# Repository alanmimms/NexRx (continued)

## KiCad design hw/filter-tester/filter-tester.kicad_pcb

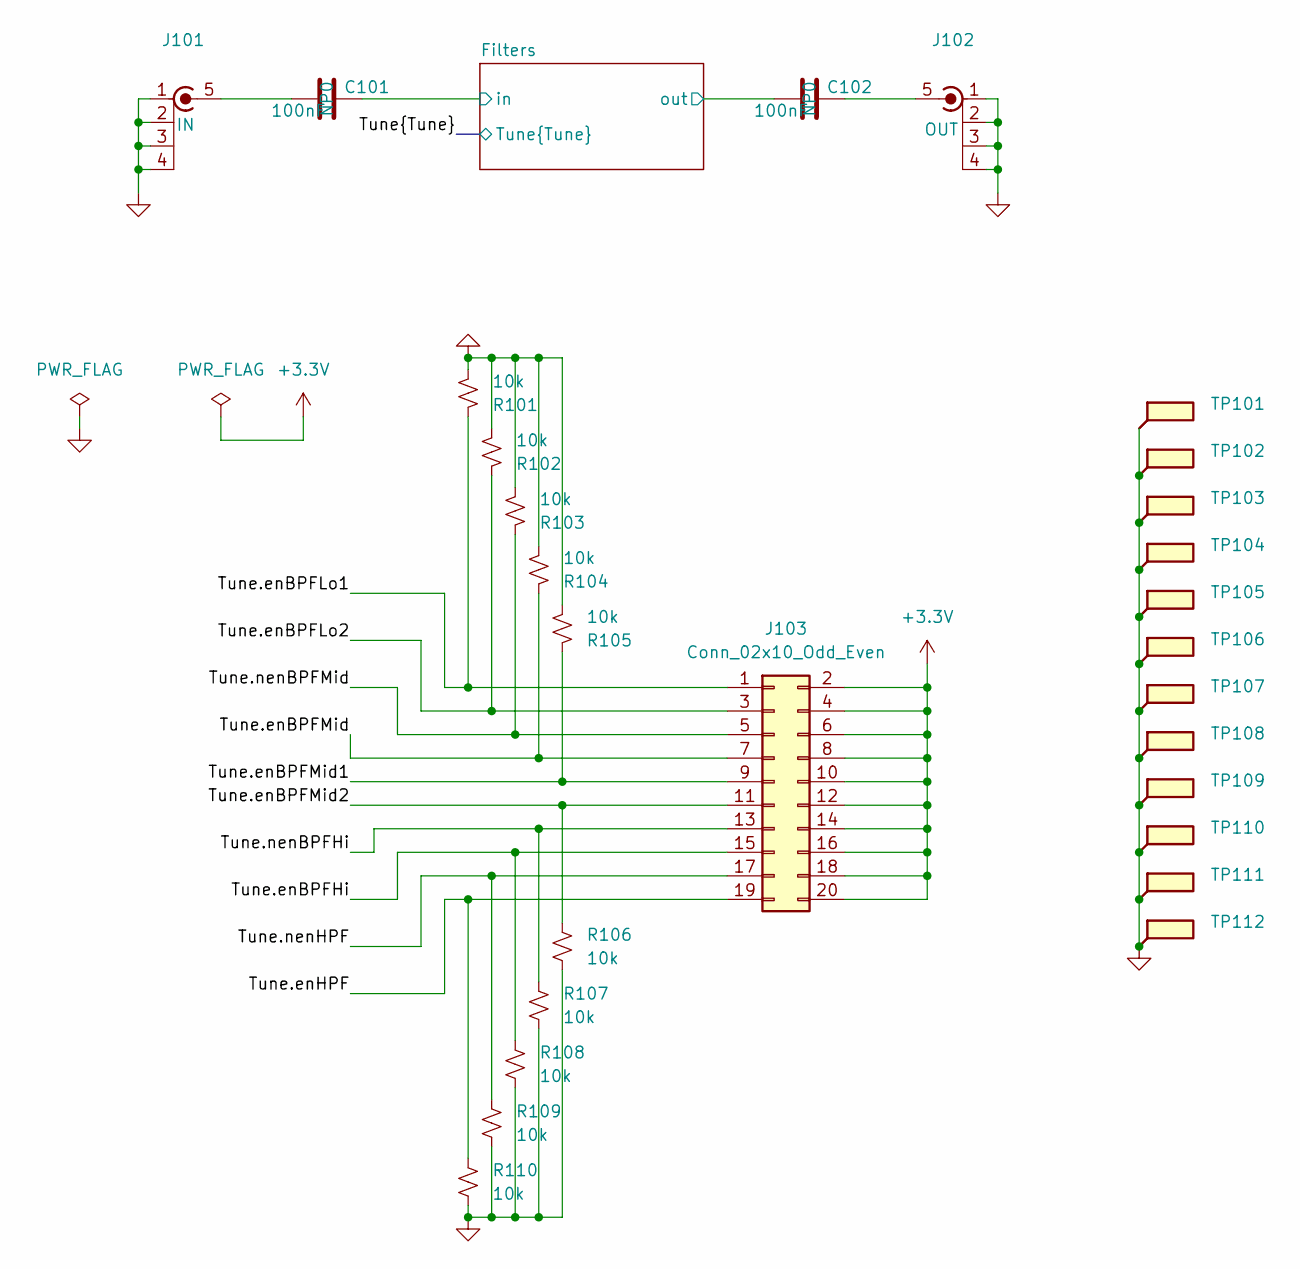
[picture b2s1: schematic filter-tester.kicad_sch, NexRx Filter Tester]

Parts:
C101, C102: 100nF; C_1206_3216Metric; MPN GRM3195C2A104JA01D; LCSC_PN C170182
J101, J102: SMA; 733910083; MPN 73391-0083; Mouser_PN 538-73391-0083
J103: Conn_02x10_Odd_Even; PinHeader_2x10_P2.54mm_Vertical_SMD; Mouser_PN 855-M20-8761046
R101, R102, R103, R104, R105, R106, R107, R108, R109, R110: 10k; R_0603_1608Metric; MPN RC0402JR-7D10KL; Mouser_PN 603-RC0402JR-7D10KL
TP101, TP102, TP103, TP104, TP105, TP106, TP107, TP108, TP109, TP110, TP111, TP112: GND; TestPoint_Pad_1.0x1.0mm

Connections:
+3.3V: J103.2, J103.4, J103.6, J103.8, J103.10, J103.12, J103.14, J103.16, J103.18, J103.20
/Filters/in: C101.1; also elsewhere on the board
/Filters/out: C102.2; also elsewhere on the board
/Tune.enBPFHi: J103.15, R108.1; also elsewhere on the board
/Tune.enBPFLo1: J103.1, R101.1; also elsewhere on the board
/Tune.enBPFLo2: J103.3, R102.1; also elsewhere on the board
/Tune.enBPFMid: J103.7, R104.1; also elsewhere on the board
/Tune.enBPFMid1: J103.9, R105.1; also elsewhere on the board
/Tune.enBPFMid2: J103.11, R106.1; also elsewhere on the board
/Tune.enHPF: J103.19, R110.1; also elsewhere on the board
/Tune.nenBPFHi: J103.13, R107.1; also elsewhere on the board
/Tune.nenBPFMid: J103.5, R103.1; also elsewhere on the board
/Tune.nenHPF: J103.17, R109.1; also elsewhere on the board
GND: J101.1 (In), J101.2 (Ext), J101.3 (Ext), J101.4 (Ext), J102.1 (In), J102.2 (Ext), J102.3 (Ext), J102.4 (Ext), R101.2, R102.2, R103.2, R104.2, R105.2, R106.2, R107.2, R108.2, R109.2, R110.2, TP101.1, TP102.1, TP103.1, TP104.1, TP105.1, TP106.1, TP107.1, TP108.1, TP109.1, TP110.1, TP111.1, TP112.1; also elsewhere on the board
unnamed: C101.2, J101.5 (Ext)
unnamed: C102.1, J102.5 (Ext)

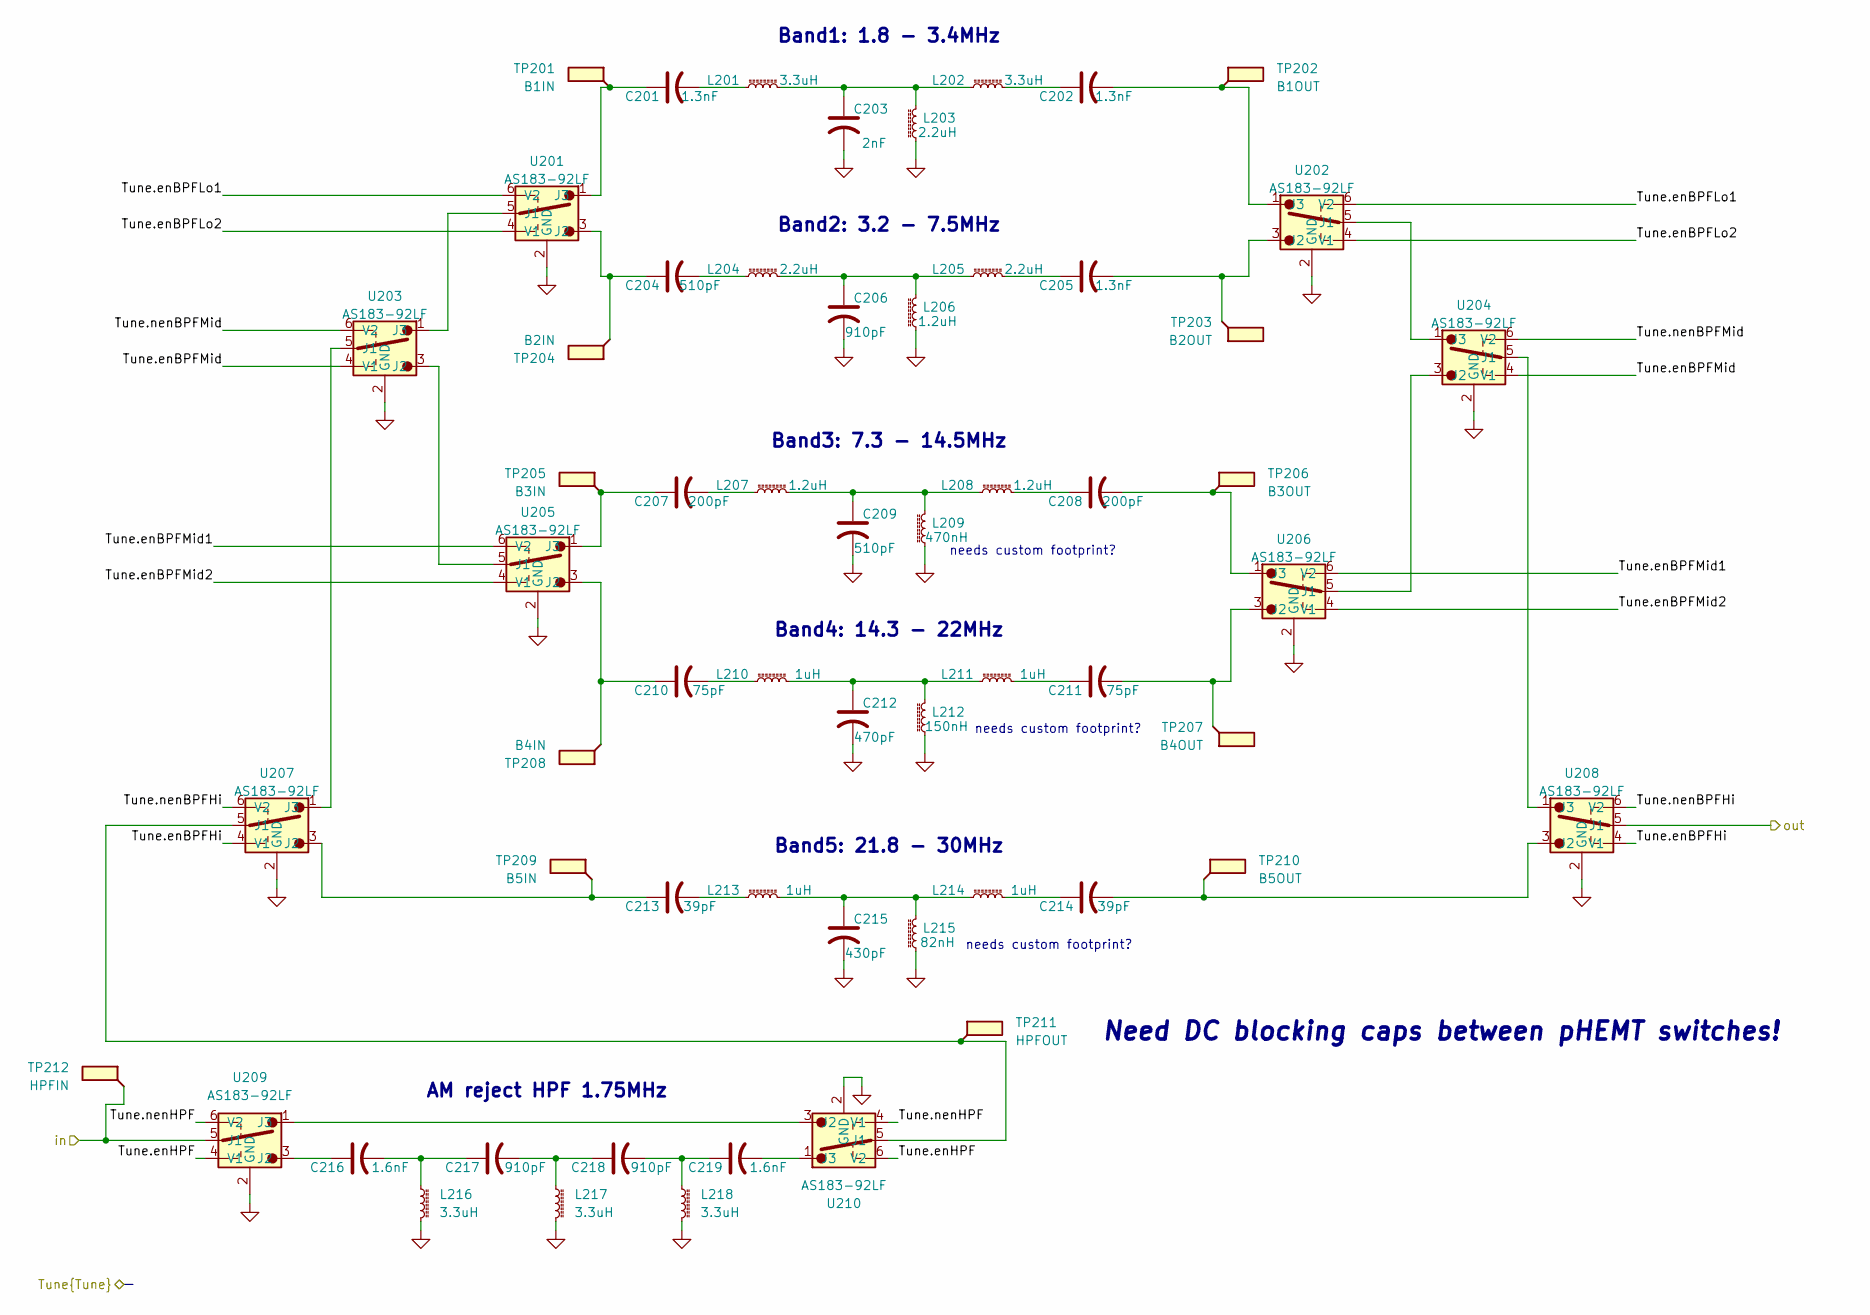
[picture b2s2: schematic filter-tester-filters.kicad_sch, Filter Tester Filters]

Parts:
C201, C202, C205: 1.3nF; C_0402_1005Metric; MPN C0402C132J5GACTU; Mouser_PN 80-C0402C132J5GACTU
C203: 2nF; C_0402_1005Metric; MPN C0402C202J3GACTU; Mouser_PN 80-C0402C202J3G
C204, C209: 510pF; C_0402_1005Metric; MPN GRT1555C1H511FA02D; Mouser_PN 81-GRT1555C1H511FA2D
C206: 910pF; C_0402_1005Metric; MPN GRT1555C1H911FA02D; Mouser_PN 81-GRT1555C1H911FA2D
C207, C208: 200pF; C_0402_1005Metric; MPN GCM1555C1H201FA16D; Mouser_PN 81-GCM1555C1H201FA6D
C210, C211: 75pF; C_0402_1005Metric; MPN GCM1555C1H750FA16J; Mouser_PN 81-GCM1555C1H750FA6J
C212: 470pF; C_0402_1005Metric; MPN GRM1555C2A471GE01D; Mouser_PN 81-GRM1555C2A471GE1D
C213, C214: 39pF; C_0402_1005Metric; MPN GRM1555C2A390JA01D; Mouser_PN 81-GRM1555C2A390JA1D
C215: 430pF; C_0402_1005Metric; MPN GRT1555C1H431FA02D; Mouser_PN 81-GRT1555C1H431FA2D
C216, C219: 1.6nF; C_0805_2012Metric; MPN GRM2165C1H162JA01D; Mouser_PN 81-GRM2165C1H162JA1D
C217, C218: 910pF; C_0805_2012Metric; MPN 08051A911JAT2A; Mouser_PN 581-08051A911JAT2A
L201, L202, L216, L217, L218: 3.3uH; L_1812_4532Metric-keepout; MPN 1812CS-332XJR; Mouser_PN 994-1812CS-332XJRC
L203, L204, L205: 2.2uH; L_1812_4532Metric-keepout; MPN 1812CS-222XJR; Mouser_PN 994-1812CS-222XJRC
L206, L207, L208: 1.2uH; L_1812_4532Metric-keepout; MPN 1812CS-122XJR; Mouser_PN 994-1812CS-122XJRC
L209: 470nH; L_1206_3216Metric-keepout; MPN AISC-1206-R47G-T; Mouser_PN 994-1206CS-471XJRC
L210, L211, L213, L214: 1uH; L_1812_4532Metric-keepout; MPN 1812CS-102XJR; Mouser_PN 994-1812CS-102XJRC
L212: 150nH; L_1206_3216Metric-keepout; MPN AISC-1206-R15G-T; Mouser_PN 994-1206CS-151XJRC
L215: 82nH; L_1206_3216Metric-keepout; MPN AISC-1206-82NK-T; Mouser_PN 994-1206CS-820XJRC
TP201: B1IN; TestPoint_Pad_1.0x1.0mm
TP202: B1OUT; TestPoint_Pad_1.0x1.0mm
TP203: B2OUT; TestPoint_Pad_1.0x1.0mm
TP204: B2IN; TestPoint_Pad_1.0x1.0mm
TP205: B3IN; TestPoint_Pad_1.0x1.0mm
TP206: B3OUT; TestPoint_Pad_1.0x1.0mm
TP207: B4OUT; TestPoint_Pad_1.0x1.0mm
TP208: B4IN; TestPoint_Pad_1.0x1.0mm
TP209: B5IN; TestPoint_Pad_1.0x1.0mm
TP210: B5OUT; TestPoint_Pad_1.0x1.0mm
TP211: HPFOUT; TestPoint_Pad_1.0x1.0mm
TP212: HPFIN; TestPoint_Pad_1.0x1.0mm
U201, U202, U203, U204, U205, U206, U207, U208, U209, U210: AS183-92LF; SOT65P220X110-6N; MPN AS183-92LF; LCSC_PN C2654768

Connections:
/Filters/in: TP212.1, U209.5 (J1); also elsewhere on the board
/Filters/out: U208.5 (J1); also elsewhere on the board
/Tune.enBPFHi: U207.4 (V1), U208.4 (V1); also elsewhere on the board
/Tune.enBPFLo1: U201.6 (V2), U202.6 (V2); also elsewhere on the board
/Tune.enBPFLo2: U201.4 (V1), U202.4 (V1); also elsewhere on the board
/Tune.enBPFMid: U203.4 (V1), U204.4 (V1); also elsewhere on the board
/Tune.enBPFMid1: U205.6 (V2), U206.6 (V2); also elsewhere on the board
/Tune.enBPFMid2: U205.4 (V1), U206.4 (V1); also elsewhere on the board
/Tune.enHPF: U209.4 (V1), U210.6 (V2); also elsewhere on the board
/Tune.nenBPFHi: U207.6 (V2), U208.6 (V2); also elsewhere on the board
/Tune.nenBPFMid: U203.6 (V2), U204.6 (V2); also elsewhere on the board
/Tune.nenHPF: U209.6 (V2), U210.4 (V1); also elsewhere on the board
GND: C203.2, C206.2, C209.2, C212.2, C215.2, L203.1, L206.1, L209.1, L212.1, L215.1, L216.2, L217.2, L218.2, U201.2 (GND), U202.2 (GND), U203.2 (GND), U204.2 (GND), U205.2 (GND), U206.2 (GND), U207.2 (GND), U208.2 (GND), U209.2 (GND), U210.2 (GND); also elsewhere on the board
unnamed: C201.2, L201.1
unnamed: C202.1, L202.2
unnamed: C203.1, L201.2, L202.1, L203.2
unnamed: C204.2, L204.1
unnamed: C205.1, L205.2
unnamed: C206.1, L204.2, L205.1, L206.2
unnamed: C207.2, L207.1
unnamed: C208.1, L208.2
unnamed: C209.1, L207.2, L208.1, L209.2
unnamed: C210.2, L210.1
unnamed: C211.1, L211.2
unnamed: C212.1, L210.2, L211.1, L212.2
unnamed: C213.2, L213.1
unnamed: C214.1, L214.2
unnamed: C215.1, L213.2, L214.1, L215.2
unnamed: C216.2, C217.1, L216.1
unnamed: C217.2, C218.1, L217.1
unnamed: C218.2, C219.1, L218.1
unnamed: U201.5 (J1), U203.1 (J3)
unnamed: C204.1, TP204.1, U201.3 (J2)
unnamed: C201.1, TP201.1, U201.1 (J3)
unnamed: U202.5 (J1), U204.1 (J3)
unnamed: C205.2, TP203.1, U202.3 (J2)
unnamed: C202.2, TP202.1, U202.1 (J3)
unnamed: U203.5 (J1), U207.1 (J3)
unnamed: U203.3 (J2), U205.5 (J1)
unnamed: U204.5 (J1), U208.1 (J3)
unnamed: U204.3 (J2), U206.5 (J1)
unnamed: C210.1, TP208.1, U205.3 (J2)
unnamed: C207.1, TP205.1, U205.1 (J3)
unnamed: C211.2, TP207.1, U206.3 (J2)
unnamed: C208.2, TP206.1, U206.1 (J3)
unnamed: TP211.1, U207.5 (J1), U210.5 (J1)
unnamed: C213.1, TP209.1, U207.3 (J2)
unnamed: C214.2, TP210.1, U208.3 (J2)
unnamed: C216.1, U209.3 (J2)
unnamed: U209.1 (J3), U210.3 (J2)
unnamed: C219.2, U210.1 (J3)

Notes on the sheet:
needs custom footprint?
AM reject HPF 1.75MHz
Band4: 14.3 - 22MHz
Need DC blocking caps between pHEMT switches!
Band3: 7.3 - 14.5MHz
Band2: 3.2 - 7.5MHz
Band5: 21.8 - 30MHz
Band1: 1.8 - 3.4MHz

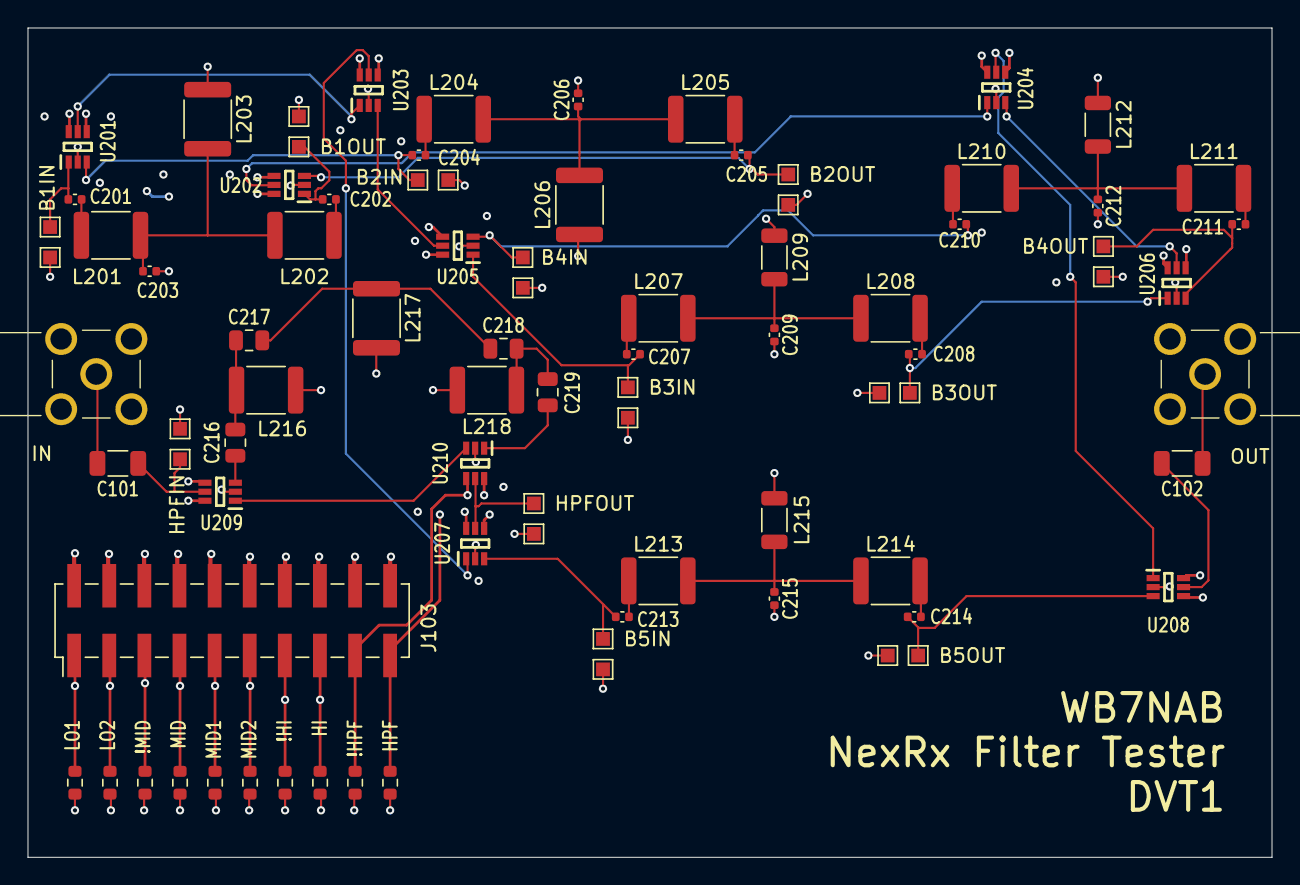
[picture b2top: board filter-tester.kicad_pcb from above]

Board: 6 copper layers, 90.0 x 60.0 mm, 86 parts (0 on the bottom side), 54 nets.

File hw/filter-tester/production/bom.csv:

Designator,Footprint,Quantity,Value,LCSC Part #
"C101, C102",1206,2,100nF,GRM3195C2A104JA01D
"C201, C202, C205",0402,3,1.3nF,C0402C132J5GACTU
C203,0402,1,2nF,C0402C202J3GACTU
"C204, C209",0402,2,510pF,GRT1555C1H511FA02D
C206,0402,1,910pF,GRT1555C1H911FA02D
"C207, C208",0402,2,200pF,GCM1555C1H201FA16D
"C210, C211",0402,2,75pF,GCM1555C1H750FA16J
C212,0402,1,470pF,GRM1555C2A471GE01D
"C213, C214",0402,2,39pF,GRM1555C2A390JA01D
C215,0402,1,430pF,GRT1555C1H431FA02D
"C216, C219",0805,2,1.6nF,GRM2165C1H162JA01D
"C217, C218",0805,2,910pF,08051A911JAT2A
"J101, J102",733910083,2,SMA,73391-0083
J103,PinHeader_2x10_P2.54mm_Vertical_SMD,1,Conn_02x10_Odd_Even,M20-8761046
"L201, L202, L216, L217, L218",1812,5,3.3uH,1812CS-332XJR
"L203, L204",1812,2,2.2uH,1812CS-222XJR
L205,1812,1,"2,2uH",1812CS-222XJR
"L206, L207, L208",1812,3,1.2uH,1812CS-122XJR
L209,1206,1,470nH,1206CS-471XJR
"L210, L211, L213, L214",1812,4,1uH,1812CS-102XJR
L212,1206,1,150nH,1206CS-151XJR
L215,1206,1,82nH,1206CS-820XJR
"R101, R102, R103, R104, R105, R106, R107, R108, R109, R110",0603,10,10k,RC0402JR-7D10KL
"TP101, TP102, TP103, TP104, TP105, TP106, TP107, TP108, TP109, TP110, TP111, TP112",TestPoint_Pad_1.0x1.0mm,12,GND,
TP201,TestPoint_Pad_1.0x1.0mm,1,B1IN,
TP202,TestPoint_Pad_1.0x1.0mm,1,B1OUT,
TP203,TestPoint_Pad_1.0x1.0mm,1,B2OUT,
TP204,TestPoint_Pad_1.0x1.0mm,1,B2IN,
TP205,TestPoint_Pad_1.0x1.0mm,1,B3IN,
TP206,TestPoint_Pad_1.0x1.0mm,1,B3OUT,
TP207,TestPoint_Pad_1.0x1.0mm,1,B4OUT,
TP208,TestPoint_Pad_1.0x1.0mm,1,B4IN,
TP209,TestPoint_Pad_1.0x1.0mm,1,B5IN,
TP210,TestPoint_Pad_1.0x1.0mm,1,B5OUT,
TP211,TestPoint_Pad_1.0x1.0mm,1,HPFOUT,
TP212,TestPoint_Pad_1.0x1.0mm,1,HPFIN,
"U201, U202, U203, U204, U205, U206, U207, U208, U209, U210",SOT65P220X110-6N,10,AS183-92LF,AS183-92LF

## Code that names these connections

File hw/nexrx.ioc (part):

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Mcu.Name=STM32H753VITx
Mcu.Package=LQFP100
Mcu.UserName=STM32H753VITx
PA0.GPIOParameters=GPIO_Label
PA0.GPIO_Label=osd0.data
PA0.Mode=SAI_B_MasterWithClock
PA0.Signal=SAI2_SD_B
PA1.GPIOParameters=GPIO_Label
PA1.GPIO_Label=osdMCLK
PA1.Mode=SAI_B_MasterWithClock
PA1.Signal=SAI2_MCLK_B
PA11.GPIOParameters=GPIO_Label
PA11.GPIO_Label=dispNSS
PA11.Mode=NSS_Signal_Hard_Output
PA11.Signal=SPI2_NSS
PA12.GPIOParameters=GPIO_Label
PA12.GPIO_Label=osdWCLK
PA12.Mode=SAI_B_MasterWithClock
PA12.Signal=SAI2_FS_B
PA13\ (JTMS/SWDIO).GPIOParameters=GPIO_Label
PA13\ (JTMS/SWDIO).GPIO_Label=SWDIO
PA13\ (JTMS/SWDIO).Mode=Serial_Wire
PA13\ (JTMS/SWDIO).Signal=DEBUG_JTMS-SWDIO
PA14\ (JTCK/SWCLK).GPIOParameters=GPIO_Label
PA14\ (JTCK/SWCLK).GPIO_Label=SWCL
PA14\ (JTCK/SWCLK).Mode=Serial_Wire
PA14\ (JTCK/SWCLK).Signal=DEBUG_JTCK-SWCLK
PA15\ (JTDI).GPIOParameters=GPIO_Speed,PinState,GPIO_Label
PA15\ (JTDI).GPIO_Label=cpld1.NSS
PA15\ (JTDI).GPIO_Speed=GPIO_SPEED_FREQ_MEDIUM
PA15\ (JTDI).PinState=GPIO_PIN_SET
PA15\ (JTDI).Signal=GPIO_Output
PA2.GPIOParameters=GPIO_Speed,GPIO_Label
PA2.GPIO_Label=osdBCLK
PA2.GPIO_Speed=GPIO_SPEED_FREQ_HIGH
PA2.Mode=SAI_B_MasterWithClock
PA2.Signal=SAI2_SCK_B
PA3.GPIOParameters=GPIO_Label
PA3.GPIO_Label=usbDATA0
PA3.Mode=Device_HS
PA3.Signal=USB_OTG_HS_ULPI_D0
PA4.GPIOParameters=GPIO_Speed,PinState,GPIO_Label
PA4.GPIO_Label=cpld0.NSS
PA4.GPIO_Speed=GPIO_SPEED_FREQ_MEDIUM
PA4.PinState=GPIO_PIN_SET
PA4.Signal=GPIO_Output
PA5.GPIOParameters=GPIO_Label
PA5.GPIO_Label=usbCLKOUT
PA5.Mode=Device_HS
PA5.Signal=USB_OTG_HS_ULPI_CK
PA6.GPIOParameters=GPIO_Label
PA6.GPIO_Label=adcReset
PA6.Signal=GPIO_Output
PA7.GPIOParameters=GPIO_Label
PA7.GPIO_Label=cc2ADC
PA7.Signal=ADCx_INP7
PA9.GPIOParameters=GPIO_Label
PA9.GPIO_Label=dispSCK
PA9.Mode=TX_Only_Simplex_Unidirect_Master
PA9.Signal=SPI2_SCK
PB0.GPIOParameters=GPIO_Label
PB0.GPIO_Label=usbDATA1
PB0.Mode=Device_HS
PB0.Signal=USB_OTG_HS_ULPI_D1
PB1.GPIOParameters=GPIO_Label
PB1.GPIO_Label=usbDATA2
PB1.Mode=Device_HS
PB1.Signal=USB_OTG_HS_ULPI_D2
PB10.GPIOParameters=GPIO_Label
PB10.GPIO_Label=usbDATA3
PB10.Mode=Device_HS
PB10.Signal=USB_OTG_HS_ULPI_D3
PB11.GPIOParameters=GPIO_Label
PB11.GPIO_Label=usbDATA4
PB11.Mode=Device_HS
PB11.Signal=USB_OTG_HS_ULPI_D4
PB12.GPIOParameters=GPIO_Label
PB12.GPIO_Label=usbDATA5
PB12.Mode=Device_HS
PB12.Signal=USB_OTG_HS_ULPI_D5
PB13.GPIOParameters=GPIO_Label
PB13.GPIO_Label=usbDATA6
PB13.Mode=Device_HS
PB13.Signal=USB_OTG_HS_ULPI_D6
PB14.GPIOParameters=GPIO_Label
PB14.GPIO_Label=factoryTX
PB14.Mode=Asynchronous
PB14.Signal=USART1_TX
PB15.GPIOParameters=GPIO_Label
PB15.GPIO_Label=factoryRX
PB15.Mode=Asynchronous
PB15.Signal=USART1_RX
PB2.GPIOParameters=GPIO_Speed,GPIO_Label
PB2.GPIO_Label=cpld.MOSI
PB2.GPIO_Speed=GPIO_SPEED_FREQ_HIGH
PB2.Mode=Full_Duplex_Master
PB2.Signal=SPI3_MOSI
PB3\ (JTDO/TRACESWO).GPIOParameters=GPIO_Label
PB3\ (JTDO/TRACESWO).GPIO_Label=gnssRESET
PB3\ (JTDO/TRACESWO).Signal=GPIO_Output
PB4\ (NJTRST).GPIOParameters=GPIO_Label
PB4\ (NJTRST).GPIO_Label=clkOEB
PB4\ (NJTRST).Signal=GPIO_Output
PB5.GPIOParameters=GPIO_Label
PB5.GPIO_Label=usbDATA7
PB5.Mode=Device_HS
PB5.Signal=USB_OTG_HS_ULPI_D7
PB6.GPIOParameters=GPIO_Label
PB6.GPIO_Label=clk.SCL
PB6.Mode=I2C
PB6.Signal=I2C1_SCL
PB7.GPIOParameters=GPIO_Label
PB7.GPIO_Label=clk.SDA
PB7.Mode=I2C
PB7.Signal=I2C1_SDA
PB8.GPIOParameters=GPIO_Label
PB8.GPIO_Label=mcuGRN
PB8.Signal=S_TIM16_CH1
PB9.GPIOParameters=GPIO_Label
PB9.GPIO_Label=mcuRED
PB9.Signal=S_TIM17_CH1
PC0.GPIOParameters=GPIO_Label
PC0.GPIO_Label=usbSTP
PC0.Mode=Device_HS
PC0.Signal=USB_OTG_HS_ULPI_STP
PC1.GPIOParameters=GPIO_Label
PC1.GPIO_Label=dispMOSI
PC1.Mode=TX_Only_Simplex_Unidirect_Master
PC1.Signal=SPI2_MOSI
PC10.GPIOParameters=GPIO_Speed,GPIO_Label
PC10.GPIO_Label=cpld.SCK
PC10.GPIO_Speed=GPIO_SPEED_FREQ_HIGH
PC10.Mode=Full_Duplex_Master
PC10.Signal=SPI3_SCK
PC11.GPIOParameters=GPIO_Speed,GPIO_Label
PC11.GPIO_Label=cpld.MISO
PC11.GPIO_Speed=GPIO_SPEED_FREQ_HIGH
PC11.Mode=Full_Duplex_Master
PC11.Signal=SPI3_MISO
PC2_C.GPIOParameters=GPIO_Label
PC2_C.GPIO_Label=usbDIR
PC2_C.Mode=Device_HS
PC2_C.Signal=USB_OTG_HS_ULPI_DIR
PC3_C.GPIOParameters=GPIO_Label
PC3_C.GPIO_Label=usbNXT
PC3_C.Mode=Device_HS
PC3_C.Signal=USB_OTG_HS_ULPI_NXT
PC5.GPIOParameters=GPIO_Label
PC5.GPIO_Label=cc1ADC
PC5.Signal=ADCx_INP8
PC7.GPIOParameters=GPIO_Label
PC7.GPIO_Label=dispBL
PC7.Signal=S_TIM3_CH2
PD0.GPIOParameters=GPIO_Label
PD0.GPIO_Label=filter.BPF2
PD0.Signal=GPIO_Output
PD1.GPIOParameters=GPIO_Label
PD1.GPIO_Label=filter.BPF1
PD1.Signal=GPIO_Output
PD10.GPIOParameters=GPIO_Label
PD10.GPIO_Label=atten.3dB
PD10.Signal=GPIO_Output
PD11.GPIOParameters=GPIO_Label
PD11.GPIO_Label=osd1.data
PD11.Mode=SAI_A_SyncSlave
PD11.Signal=SAI2_SD_A
PD2.GPIOParameters=GPIO_Label
PD2.GPIO_Label=filter.HPF
PD2.Signal=GPIO_Output
PD3.GPIOParameters=GPIO_Label
PD3.GPIO_Label=filter.nHPF
PD3.Signal=GPIO_Output
PD4.GPIOParameters=GPIO_Label
PD4.GPIO_Label=filter.BPF4
PD4.Signal=GPIO_Output
PD5.GPIOParameters=GPIO_Label
PD5.GPIO_Label=filter.BPF3
PD5.Signal=GPIO_Output
PD6.GPIOParameters=GPIO_Label
PD6.GPIO_Label=enable3V3
PD6.Signal=GPIO_Output
PD7.GPIOParameters=GPIO_Label
PD7.GPIO_Label=atten.6dB
PD7.Signal=GPIO_Output
PD8.GPIOParameters=GPIO_Label
PD8.GPIO_Label=atten.12dB
PD8.Signal=GPIO_Output
PD9.GPIOParameters=GPIO_Label
PD9.GPIO_Label=atten.24dB
PD9.Signal=GPIO_Output
PE0.GPIOParameters=GPIO_Label
PE0.GPIO_Label=cpldDONE
PE0.Signal=GPIO_Input
PE1.GPIOParameters=GPIO_Label
PE1.GPIO_Label=cpld.CRESET
PE1.Signal=GPIO_Output
PE12.GPIOParameters=GPIO_Label
PE12.GPIO_Label=dispRESET
PE12.Signal=GPIO_Output
PE13.GPIOParameters=GPIO_Speed,GPIO_Label
PE13.GPIO_Label=dispDC
PE13.GPIO_Speed=GPIO_SPEED_FREQ_MEDIUM
PE13.Signal=GPIO_Output
PE14.GPIOParameters=GPIO_Speed,GPIO_Label
PE14.GPIO_Label=osdMOSI
PE14.GPIO_Speed=GPIO_SPEED_FREQ_HIGH
PE14.Mode=Full_Duplex_Master
PE14.Signal=SPI4_MOSI
PE2.GPIOParameters=GPIO_Speed,GPIO_Label
PE2.GPIO_Label=osdSCK
PE2.GPIO_Speed=GPIO_SPEED_FREQ_HIGH
PE2.Mode=Full_Duplex_Master
PE2.Signal=SPI4_SCK
PE3.GPIOParameters=GPIO_Speed,GPIO_Label
PE3.GPIO_Label=osd0.NSS
PE3.GPIO_Speed=GPIO_SPEED_FREQ_MEDIUM
PE3.Signal=GPIO_Output
PE4.GPIOParameters=GPIO_Speed,GPIO_Label
PE4.GPIO_Label=osd1.NSS
PE4.GPIO_Speed=GPIO_SPEED_FREQ_MEDIUM
PE4.Signal=GPIO_Output
PE5.GPIOParameters=GPIO_Label
PE5.GPIO_Label=osdMISO
PE5.Mode=Full_Duplex_Master
PE5.Signal=SPI4_MISO
PE6.GPIOParameters=GPIO_Label
PE6.GPIO_Label=mcuBLU
PE6.Signal=S_TIM15_CH2
PE7.GPIOParameters=GPIO_Label
PE7.GPIO_Label=gnssRx
PE7.Mode=Asynchronous
PE7.Signal=UART7_RX
PE8.GPIOParameters=GPIO_Label
PE8.GPIO_Label=gnssTx
PE8.Mode=Asynchronous
PE8.Signal=UART7_TX
PH0-OSC_IN\ (PH0).Mode=HSE-External-Oscillator
PH0-OSC_IN\ (PH0).Signal=RCC_OSC_IN
PH1-OSC_OUT\ (PH1).Mode=HSE-External-Oscillator
PH1-OSC_OUT\ (PH1).Signal=RCC_OSC_OUT
RCC.SYSCLKFreq_VALUE=64000000
board=custom

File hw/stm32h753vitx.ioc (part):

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Mcu.Name=STM32H753VITx
Mcu.Package=LQFP100
Mcu.UserName=STM32H753VITx
PA0.GPIOParameters=GPIO_Label
PA0.GPIO_Label=Ctrl.qsdData2
PA0.Mode=SAI_B_SyncSlave
PA0.Signal=SAI2_SD_B
PA11.GPIOParameters=GPIO_Label
PA11.GPIO_Label=dispNSS
PA11.Mode=NSS_Signal_Hard_Output
PA11.Signal=SPI2_NSS
PA13\ (JTMS/SWDIO).GPIOParameters=GPIO_Label
PA13\ (JTMS/SWDIO).GPIO_Label=SWDIO
PA13\ (JTMS/SWDIO).Mode=Serial_Wire
PA13\ (JTMS/SWDIO).Signal=DEBUG_JTMS-SWDIO
PA14\ (JTCK/SWCLK).GPIOParameters=GPIO_Label
PA14\ (JTCK/SWCLK).GPIO_Label=SWCL
PA14\ (JTCK/SWCLK).Mode=Serial_Wire
PA14\ (JTCK/SWCLK).Signal=DEBUG_JTCK-SWCLK
PA3.GPIOParameters=GPIO_Label
PA3.GPIO_Label=usbDATA0
PA3.Mode=Device_HS
PA3.Signal=USB_OTG_HS_ULPI_D0
PA4.GPIOParameters=GPIO_Label,GPIO_Speed,GPIO_PuPd
PA4.GPIO_Label=FPGA.NSS
PA4.GPIO_PuPd=GPIO_PULLUP
PA4.GPIO_Speed=GPIO_SPEED_FREQ_HIGH
PA4.Mode=NSS_Signal_Hard_Output
PA4.Signal=SPI3_NSS
PA5.GPIOParameters=GPIO_Label
PA5.GPIO_Label=usbCLKOUT
PA5.Mode=Device_HS
PA5.Signal=USB_OTG_HS_ULPI_CK
PA6.GPIOParameters=GPIO_Label
PA6.GPIO_Label=Ctrl.audioReset
PA6.Signal=GPIO_Output
PA7.GPIOParameters=GPIO_Label
PA7.GPIO_Label=Ctrl.usbCC2adc
PA7.Signal=ADCx_INP7
PA9.GPIOParameters=GPIO_Label
PA9.GPIO_Label=dispSCK
PA9.Mode=TX_Only_Simplex_Unidirect_Master
PA9.Signal=SPI2_SCK
PB0.GPIOParameters=GPIO_Label
PB0.GPIO_Label=usbDATA1
PB0.Mode=Device_HS
PB0.Signal=USB_OTG_HS_ULPI_D1
PB1.GPIOParameters=GPIO_Label
PB1.GPIO_Label=usbDATA2
PB1.Mode=Device_HS
PB1.Signal=USB_OTG_HS_ULPI_D2
PB10.GPIOParameters=GPIO_Label
PB10.GPIO_Label=usbDATA3
PB10.Mode=Device_HS
PB10.Signal=USB_OTG_HS_ULPI_D3
PB11.GPIOParameters=GPIO_Label
PB11.GPIO_Label=usbDATA4
PB11.Mode=Device_HS
PB11.Signal=USB_OTG_HS_ULPI_D4
PB12.GPIOParameters=GPIO_Label
PB12.GPIO_Label=usbDATA5
PB12.Mode=Device_HS
PB12.Signal=USB_OTG_HS_ULPI_D5
PB13.GPIOParameters=GPIO_Label
PB13.GPIO_Label=usbDATA6
PB13.Mode=Device_HS
PB13.Signal=USB_OTG_HS_ULPI_D6
PB2.GPIOParameters=GPIO_Speed,GPIO_Label
PB2.GPIO_Label=FPGA.MOSI
PB2.GPIO_Speed=GPIO_SPEED_FREQ_HIGH
PB2.Mode=Full_Duplex_Master
PB2.Signal=SPI3_MOSI
PB5.GPIOParameters=GPIO_Label
PB5.GPIO_Label=usbDATA7
PB5.Mode=Device_HS
PB5.Signal=USB_OTG_HS_ULPI_D7
PC0.GPIOParameters=GPIO_Label
PC0.GPIO_Label=usbSTP
PC0.Mode=Device_HS
PC0.Signal=USB_OTG_HS_ULPI_STP
PC1.GPIOParameters=GPIO_Label
PC1.GPIO_Label=dispMOSI
PC1.Mode=TX_Only_Simplex_Unidirect_Master
PC1.Signal=SPI2_MOSI
PC10.GPIOParameters=GPIO_Speed,GPIO_Label
PC10.GPIO_Label=FPGA.SCK
PC10.GPIO_Speed=GPIO_SPEED_FREQ_HIGH
PC10.Mode=Full_Duplex_Master
PC10.Signal=SPI3_SCK
PC11.GPIOParameters=GPIO_Speed,GPIO_Label
PC11.GPIO_Label=FPGA.MISO
PC11.GPIO_Speed=GPIO_SPEED_FREQ_HIGH
PC11.Mode=Full_Duplex_Master
PC11.Signal=SPI3_MISO
PC2_C.GPIOParameters=GPIO_Label
PC2_C.GPIO_Label=usbDIR
PC2_C.Mode=Device_HS
PC2_C.Signal=USB_OTG_HS_ULPI_DIR
PC3_C.GPIOParameters=GPIO_Label
PC3_C.GPIO_Label=usbNXT
PC3_C.Mode=Device_HS
PC3_C.Signal=USB_OTG_HS_ULPI_NXT
PC5.GPIOParameters=GPIO_Label
PC5.GPIO_Label=Ctrl.usbCC1adc
PC5.Signal=ADCx_INP8
PC6.GPIOParameters=GPIO_Label
PC6.GPIO_Label=Tune.txrx
PC6.Mode=Half_duplex(single_wire_mode)
PC6.Signal=USART6_TX
PD0.GPIOParameters=GPIO_Speed,GPIO_Label
PD0.GPIO_Label=Ctrl.qsdBCLK
PD0.GPIO_Speed=GPIO_SPEED_FREQ_HIGH
PD0.Mode=SAI_A_MasterWithClock
PD0.Signal=SAI3_SCK_A
PD1.GPIOParameters=GPIO_Speed,GPIO_Label
PD1.GPIO_Label=Ctrl.qsdData1
PD1.GPIO_Speed=GPIO_SPEED_FREQ_HIGH
PD1.Mode=SAI_A_MasterWithClock
PD1.Signal=SAI3_SD_A
PD11.GPIOParameters=GPIO_Label
PD11.GPIO_Label=Ctrl.qsdData3
PD11.Mode=SAI_A_SyncSlave
PD11.Signal=SAI2_SD_A
PD12.GPIOParameters=GPIO_Speed,GPIO_Label
PD12.GPIO_Label=Ctrl.audioSCL
PD12.GPIO_Speed=GPIO_SPEED_FREQ_MEDIUM
PD12.Mode=I2C
PD12.Signal=I2C4_SCL
PD13.GPIOParameters=GPIO_Speed,GPIO_Label
PD13.GPIO_Label=Ctrl.audioSDA
PD13.GPIO_Speed=GPIO_SPEED_FREQ_MEDIUM
PD13.Mode=I2C
PD13.Signal=I2C4_SDA
PD15.GPIOParameters=GPIO_Speed,GPIO_Label
PD15.GPIO_Label=Ctrl.qsdMCLK
PD15.GPIO_Speed=GPIO_SPEED_FREQ_HIGH
PD15.Mode=SAI_A_MasterWithClock
PD15.Signal=SAI3_MCLK_A
PD4.GPIOParameters=GPIO_Speed,GPIO_Label
PD4.GPIO_Label=Ctrl.qsdWCLK
PD4.GPIO_Speed=GPIO_SPEED_FREQ_HIGH
PD4.Mode=SAI_A_MasterWithClock
PD4.Signal=SAI3_FS_A
PD5.Signal=GPIO_Output
PD6.GPIOParameters=GPIO_Label
PD6.GPIO_Label=Ctrl.enable3V3
PD6.Signal=GPIO_Output
PD7.GPIOParameters=GPIO_Label
PD7.GPIO_Label=Ctrl.enable3VA
PD7.Signal=GPIO_Output
PD8.GPIOParameters=GPIO_Label
PD8.GPIO_Label=Ctrl.enable5VA
PD8.Signal=GPIO_Output
PD9.GPIOParameters=GPIO_Label
PD9.GPIO_Label=Ctrl.enableFPGAVCORE
PD9.Signal=GPIO_Output
PE0.GPIOParameters=GPIO_Label
PE0.GPIO_Label=FPGA.DONE
PE0.Signal=GPIO_Input
PE1.GPIOParameters=GPIO_Label
PE1.GPIO_Label=FPGA.PROG
PE1.Signal=GPIO_Output
PE12.GPIOParameters=GPIO_Label
PE12.GPIO_Label=dispRESET
PE12.Signal=GPIO_Output
PE13.GPIOParameters=GPIO_Label
PE13.GPIO_Label=dispDC
PE13.Signal=GPIO_Output
PE14.GPIOParameters=GPIO_Label,GPIO_Speed
PE14.GPIO_Label=Ctrl.pgaMOSI
PE14.GPIO_Speed=GPIO_SPEED_FREQ_HIGH
PE14.Mode=TX_Only_Simplex_Unidirect_Master
PE14.Signal=SPI4_MOSI
PE2.GPIOParameters=GPIO_Speed,GPIO_Label
PE2.GPIO_Label=Ctrl.pgaSCK
PE2.GPIO_Speed=GPIO_SPEED_FREQ_HIGH
PE2.Mode=TX_Only_Simplex_Unidirect_Master
PE2.Signal=SPI4_SCK
PE3.Signal=GPIO_Input
PE4.GPIOParameters=GPIO_Speed,GPIO_PuPd,GPIO_Label
PE4.GPIO_Label=Ctrl.pgaNSS
PE4.GPIO_PuPd=GPIO_PULLUP
PE4.GPIO_Speed=GPIO_SPEED_FREQ_HIGH
PE4.Mode=NSS_Signal_Hard_Output
PE4.Signal=SPI4_NSS
PE6.GPIOParameters=GPIO_Label
PE6.GPIO_Label=Ctrl.qsdData4
PE6.Mode=SAI_A_SyncSlave
PE6.Signal=SAI4_SD_A
PH0-OSC_IN\ (PH0).GPIOParameters=GPIO_Label
PH0-OSC_IN\ (PH0).GPIO_Label=STM32Clock
PH0-OSC_IN\ (PH0).Mode=HSE-External-Clock-Source
PH0-OSC_IN\ (PH0).Signal=RCC_OSC_IN
RCC.SYSCLKFreq_VALUE=64000000
board=custom

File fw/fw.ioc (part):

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Mcu.Name=STM32H753ZITx
Mcu.Package=LQFP144
Mcu.UserName=STM32H753ZITx
PA13\ (JTMS/SWDIO).GPIOParameters=GPIO_Label
PA13\ (JTMS/SWDIO).GPIO_Label=SWDIO
PA13\ (JTMS/SWDIO).Mode=Serial_Wire
PA13\ (JTMS/SWDIO).Signal=DEBUG_JTMS-SWDIO
PA14\ (JTCK/SWCLK).GPIOParameters=GPIO_Label
PA14\ (JTCK/SWCLK).GPIO_Label=SWCL
PA14\ (JTCK/SWCLK).Mode=Serial_Wire
PA14\ (JTCK/SWCLK).Signal=DEBUG_JTCK-SWCLK
PA15\ (JTDI).GPIOParameters=GPIO_Speed,GPIO_PuPd,GPIO_Label
PA15\ (JTDI).GPIO_Label=FPGA_NSS
PA15\ (JTDI).GPIO_PuPd=GPIO_PULLUP
PA15\ (JTDI).GPIO_Speed=GPIO_SPEED_FREQ_MEDIUM
PA15\ (JTDI).Mode=NSS_Signal_Hard_Output
PA15\ (JTDI).Signal=SPI3_NSS
PA3.GPIOParameters=GPIO_Label
PA3.GPIO_Label=usbDATA0
PA3.Mode=Device_HS
PA3.Signal=USB_OTG_HS_ULPI_D0
PA5.GPIOParameters=GPIO_Label
PA5.GPIO_Label=usbCLKOUT
PA5.Mode=Device_HS
PA5.Signal=USB_OTG_HS_ULPI_CK
PA6.GPIOParameters=GPIO_PuPd,GPIO_Label
PA6.GPIO_Label=Ctrl_audioReset
PA6.GPIO_PuPd=GPIO_PULLDOWN
PA6.Signal=GPIO_Output
PA7.GPIOParameters=GPIO_Label
PA7.GPIO_Label=Ctrl.usbCC2adc
PA7.Signal=ADCx_INP7
PB0.GPIOParameters=GPIO_Label
PB0.GPIO_Label=usbDATA1
PB0.Mode=Device_HS
PB0.Signal=USB_OTG_HS_ULPI_D1
PB1.GPIOParameters=GPIO_Label
PB1.GPIO_Label=usbDATA2
PB1.Mode=Device_HS
PB1.Signal=USB_OTG_HS_ULPI_D2
PB10.GPIOParameters=GPIO_Label
PB10.GPIO_Label=usbDATA3
PB10.Mode=Device_HS
PB10.Signal=USB_OTG_HS_ULPI_D3
PB11.GPIOParameters=GPIO_Label
PB11.GPIO_Label=usbDATA4
PB11.Mode=Device_HS
PB11.Signal=USB_OTG_HS_ULPI_D4
PB12.GPIOParameters=GPIO_Label
PB12.GPIO_Label=usbDATA5
PB12.Mode=Device_HS
PB12.Signal=USB_OTG_HS_ULPI_D5
PB13.GPIOParameters=GPIO_Label
PB13.GPIO_Label=usbDATA6
PB13.Mode=Device_HS
PB13.Signal=USB_OTG_HS_ULPI_D6
PB2.GPIOParameters=GPIO_Label
PB2.GPIO_Label=Ctrl.qsdData
PB2.Mode=SAI_A_MasterWithClock
PB2.Signal=SAI1_SD_A
PB3\ (JTDO/TRACESWO).Signal=DEBUG_JTDO-SWO
PB5.GPIOParameters=GPIO_Label
PB5.GPIO_Label=usbDATA7
PB5.Mode=Device_HS
PB5.Signal=USB_OTG_HS_ULPI_D7
PC0.GPIOParameters=GPIO_Label
PC0.GPIO_Label=usbSTP
PC0.Mode=Device_HS
PC0.Signal=USB_OTG_HS_ULPI_STP
PC10.GPIOParameters=GPIO_Speed,GPIO_Label
PC10.GPIO_Label=FPGA_SCK
PC10.GPIO_Speed=GPIO_SPEED_FREQ_HIGH
PC10.Mode=Full_Duplex_Master
PC10.Signal=SPI3_SCK
PC11.GPIOParameters=GPIO_PuPd,GPIO_Label
PC11.GPIO_Label=FPGA_MISO
PC11.GPIO_PuPd=GPIO_PULLUP
PC11.Mode=Full_Duplex_Master
PC11.Signal=SPI3_MISO
PC12.GPIOParameters=GPIO_Speed,GPIO_Label
PC12.GPIO_Label=FPGA_MOSI
PC12.GPIO_Speed=GPIO_SPEED_FREQ_HIGH
PC12.Mode=Full_Duplex_Master
PC12.Signal=SPI3_MOSI
PC2_C.GPIOParameters=GPIO_Label
PC2_C.GPIO_Label=usbDIR
PC2_C.Mode=Device_HS
PC2_C.Signal=USB_OTG_HS_ULPI_DIR
PC3_C.GPIOParameters=GPIO_Label
PC3_C.GPIO_Label=usbNXT
PC3_C.Mode=Device_HS
PC3_C.Signal=USB_OTG_HS_ULPI_NXT
PD12.GPIOParameters=GPIO_Speed,GPIO_Label,GPIO_Pu
PD12.GPIO_Label=Ctrl_audioSCL
PD12.GPIO_Pu=GPIO_NOPULL
PD12.GPIO_Speed=GPIO_SPEED_FREQ_MEDIUM
PD12.Mode=I2C
PD12.Signal=I2C4_SCL
PD7.GPIOParameters=GPIO_Speed,GPIO_Label
PD7.GPIO_Label=dispMOSI
PD7.GPIO_Speed=GPIO_SPEED_FREQ_HIGH
PD7.Mode=TX_Only_Simplex_Unidirect_Master
PD7.Signal=SPI1_MOSI
PE0.GPIOParameters=GPIO_PuPd,GPIO_Label
PE0.GPIO_Label=CDONE
PE0.GPIO_PuPd=GPIO_PULLDOWN
PE0.Signal=GPIO_Input
PE11.GPIOParameters=GPIO_PuPd,GPIO_Label
PE11.GPIO_Label=Ctrl.qsdNSS
PE11.GPIO_PuPd=GPIO_PULLUP
PE11.Mode=NSS_Signal_Hard_Output
PE11.Signal=SPI4_NSS
PE12.GPIOParameters=GPIO_PuPd,GPIO_Label
PE12.GPIO_Label=dispRESET
PE12.GPIO_PuPd=GPIO_PULLDOWN
PE12.Signal=GPIO_Output
PE13.GPIOParameters=GPIO_Label
PE13.GPIO_Label=dispDC
PE13.Signal=GPIO_Output
PE15.GPIOParameters=GPIO_PuPd,GPIO_Label
PE15.GPIO_Label=FPGA.RESET
PE15.GPIO_PuPd=GPIO_PULLDOWN
PE15.Signal=GPIO_Output
PE2.GPIOParameters=GPIO_Speed,GPIO_Label
PE2.GPIO_Label=Ctrl.qsdSCK
PE2.GPIO_Speed=GPIO_SPEED_FREQ_HIGH
PE2.Mode=TX_Only_Simplex_Unidirect_Master
PE2.Signal=SPI4_SCK
PE4.GPIOParameters=GPIO_Label
PE4.GPIO_Label=Ctrl.qsdWCLK
PE4.Mode=SAI_A_MasterWithClock
PE4.Signal=SAI1_FS_A
PE5.GPIOParameters=GPIO_Label
PE5.GPIO_Label=Ctrl.qsdBCLK
PE5.Mode=SAI_A_MasterWithClock
PE5.Signal=SAI1_SCK_A
PE6.GPIOParameters=GPIO_Label
PE6.GPIO_Label=Ctrl.qsdMOSI
PE6.Mode=TX_Only_Simplex_Unidirect_Master
PE6.Signal=SPI4_MOSI
PF0.GPIOParameters=GPIO_Label
PF0.GPIO_Label=Ctrl.enable6V
PF0.Signal=GPIO_Output
PF1.GPIOParameters=GPIO_Label
PF1.GPIO_Label=Ctrl.enable3V3
PF1.Signal=GPIO_Output
PF12.GPIOParameters=GPIO_Label
PF12.GPIO_Label=Ctrl.usbCC1adc
PF12.Mode=IN6-Single-Ended
PF12.Signal=ADC1_INP6
PF14.Signal=GPIO_Input
PF15.GPIOParameters=GPIO_Speed,GPIO_Label,GPIO_Pu
PF15.GPIO_Label=Ctrl_audioSDA
PF15.GPIO_Pu=GPIO_NOPULL
PF15.GPIO_Speed=GPIO_SPEED_FREQ_MEDIUM
PF15.Mode=I2C
PF15.Signal=I2C4_SDA
PF3.GPIOParameters=GPIO_Label
PF3.GPIO_Label=Ctrl.enable3VA
PF3.Signal=GPIO_Output
PF4.GPIOParameters=GPIO_Label
PF4.GPIO_Label=Ctrl.enable5VA
PF4.Signal=GPIO_Output
PF5.GPIOParameters=GPIO_Label
PF5.GPIO_Label=Ctrl.enableFPGA1V2
PF5.Signal=GPIO_Output
PG10.GPIOParameters=GPIO_Speed,GPIO_PuPd,GPIO_Label
PG10.GPIO_Label=dispNSS
PG10.GPIO_PuPd=GPIO_PULLUP
PG10.GPIO_Speed=GPIO_SPEED_FREQ_MEDIUM
PG10.Mode=NSS_Signal_Hard_Output
PG10.Signal=SPI1_NSS
PG11.GPIOParameters=GPIO_Speed,GPIO_Label
PG11.GPIO_Label=dispSCK
PG11.GPIO_Speed=GPIO_SPEED_FREQ_HIGH
PG11.Mode=TX_Only_Simplex_Unidirect_Master
PG11.Signal=SPI1_SCK
PG7.GPIOParameters=GPIO_Label
PG7.GPIO_Label=Ctrl.qsdMCLK
PG7.Mode=SAI_A_MasterWithClock
PG7.Signal=SAI1_MCLK_A
PH0-OSC_IN\ (PH0).GPIOParameters=GPIO_Label
PH0-OSC_IN\ (PH0).GPIO_Label=STM32clock
PH0-OSC_IN\ (PH0).Mode=HSE-External-Clock-Source
PH0-OSC_IN\ (PH0).Signal=RCC_OSC_IN
RCC.SYSCLKFreq_VALUE=64000000
board=custom

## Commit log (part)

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2026-01-19 Note some TODOs for the UI
2026-01-25 Tweak position of refdes/label for audio codec so I can FIND it in the complexity
2026-02-03 Checkpoint with all rf200 routed, much diff pair work done, Now it's basically bog standard control logic routing left
2026-02-05 All tracks routed. Now for a SHITLOAD of DRC fixes.
2026-02-07 A few more tweaks to checkpoint
2026-02-16 Reorient FPGA for routing, clean up transition (back) to ICE40UP5K part. Add series R in fast long SPI bus signals going to multi-drop MAX9939 control bus.
2026-02-18 Remove mention of older AS169-73LF part we have switched to AS183-92LF instead.
2026-02-18 Fix up docs to make this NexRx (receiver project) specific and eliminate all but elliptical references to NexRig (the transceiver)
2026-02-18 tools: add BOM management and PCB audit utilities, setup production outputs
2026-02-18 Remove unused sch page
2026-02-19 Document the power architecture
2026-02-19 Fix up more AI induced insanity
2026-02-20 I switched to a simpler package for this LDO
2026-02-22 Checkpoint reverting away from VLF extension
2026-02-24 Routing completely revamped for 200 ohm traces and attenuators and preselector and related. Tantalum cap footprint change has been built into the bias supply. General clean up. 3D now renders all the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
2026-02-25 Define nexbus (stupid name) and rules for GEMINI to help me better
2026-02-26 I was going to eliminate the "Tune" bus, but it is still used between GPIO expanders and the rx preselector, so I backed that out.
2026-02-26 New FPGA "intSigGen" PDM based signal generator with attenuator for calibrations and testing
2026-02-26 Enhance ISG controls and fix long-term stability issues
    * Implement frequency typing for ISG display via new input mode.
    * Add comprehensive mouse wheel tuning modifiers for ISG control.
    * Transition Digital Twin to phase accumulators for RF, LO, and ISG to fix long-term precision loss and images.
    * Implement frequency-based ISG rejection (8th-order Butterworth) to prevent aliasing when tuned far-off.
    * Reduce ISG level to 5uV and remove automatic 45dB attenuation safety.
    * Fix stimulus generator discontinuities on simulation time resets.
2026-02-26 Add WWV ident to test AM modulation in STYLE
2026-02-27 Add some tools to do various selecting things so I can build the keepout rules for rf200 impedance zone. Fix up a bunch of annoyingly untidy items. Route grounds with traces WITHIN the 200 ohm zone t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
2026-02-28 Consolidate BOM management and back-propagate properties to schematics
    * Implement unified BOM processor (tools/bom-processor.py) using kicad-cli for macro expansion and field collapsing.
    * Back-propagate unified component properties (Manufacturer, MPN, LCSC_PN, Mouser_PN, Description) to all KiCad schematic files.
    * Generate initial production BOM (production/nexrx-bom.csv) with 100% LCSC part number coverage.
    * Standardize passive component descriptions with full technical specifications (dielectric, voltage, tolerance).
    * Clean up redundant manufacturer and part number fields in schematic symbols.
    * Remove obsolete BOM management scripts.
2026-02-28 Implement hardware inaccuracy simulation and detailed preselector characterization
    * Twin: Add simulation of random hardware I/Q gain and phase inaccuracies per channel.
    * Twin: Implement physical preselector model with corrected 11-bit binary-weighted capacitor bank (8pF to 8nF).
    * Twin: Fix ISG logic to support tone mode (>1Hz), white noise (1Hz), and disabled (0Hz).
    * Twin: Add digital resonator filter for ISG white noise mode to simulate passband shape in FFT.
    * Twin: Add --cal-file and --no-cal flags; report simulated errors on startup.
    * Test-App: Expand preselector characterization to 31 representative masks with detailed reporting (Peak, -3dB BW, Q).
2026-02-28 Added support for four audio serial links from AK5578 codec to STM32H753, each with 22 ohm series R and I put series R in the clock outputs from STM32 toward AK5578 as well. Reannotated.
2026-03-04 Move LICENSE to the top - it covers everything
2026-03-04 Complete base firmware infrastructure and modular integration
    - Implemented DisplayManager for ST7789V LCD status reporting.
    - Added USB Control Plane with CBOR command dispatcher over CDC-ACM.
    - Integrated high-speed USB v3 Bulk Offload for I/Q data streaming.
    - Implemented NexBus Mode B (UART) for runtime firmware updates of C011 expanders.
    - Added dynamic pinctrl switching for multi-mode pin multiplexing on PC6.
    - Finalized modular integration of all hardware drivers and transport layers.
2026-03-04 Align App and Twin with hardware protocols and Version 2 binary format
    - Refactored UDPStreamTransport and UDPStreamClient to fix UPD typo and use Version 2 binary data plane.
    - Updated TwinConn and ControlHandler to use flatter CBOR command structures matching the MCU firmware.
    - Aligned all symbol names to follow project rules (all-caps acronyms, camelCase members).
    - Renamed all transport and connection source files to use hyphenated naming.
    - Synchronized signalgen.cpp logic with FPGA NCO behaviors.
    - Refactored Orchestrator and other twin components for consistent modularity and naming.
2026-03-05 Generalize control plane with uint32_t command IDs and align SetBox defaults
    Refactor application, twin, and firmware to use a unified control protocol based on uint32_t command IDs. Update AppState to pull all initial settings from SetBox rules, centering volume and RF gain 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
2026-03-06 Implement Triple-QSD architecture and accurate preselector physics
    - Refactored preselector logic in app and twin with realistic LC tank model
    - Fixed preselector auto-tune initialization and L/C logic inversion
    - Implemented Hilbert transform for high-fidelity SSB phasing in Demodulator
    - Refined LMS adaptive filtering and baseband combining for image rejection
    - Updated control protocol to use atomic bitmasks for preselector state
    - Added spectrum graticule legend and improved UI state reactivity
2026-03-07 Modularize sidebar widgets and fix crash in WaterfallRenderer
    - Split ISG, AGC, and AudioUtils into standalone modules
    - Implement solveDynamicSublayout for SetBox-driven sidebar ordering
    - Fix WaterfallRenderer::renderSpectrum segfault and GL state errors
    - Correct sidebar height calculations for top-anchored layout
    - Restore drawRoundedRect and fix font initialization sequence
2026-03-07 Refactor UI widgets to OOP model and enforce strict SetBox rules
    - Convert all low-level UI components (Label, Button, Checkbox, Slider, Panel, SMeter, ActiveTags, GraticuleLegend, FrequencyDisplay) into standalone PascalCase object classes
    - Rename container.lua and constraints.lua to PascalCase (Container.lua, Constraints.lua)
    - Update setbox.lua to enforce strict rule-based property resolution by removing default-parameter fallbacks from all getters
    - Refactor main.lua to use new widget objects and eliminate hardcoded labels/styling
    - Move all UI strings (e.g., 'ACTIVE TAGS', 'Mode', 'Band') into SetBox rules in default.lua
    - Improve S-meter scaling and normalize RMS-to-dBm offset for dig
2026-03-08 Fix global state leakage, restore container titles, and finalize rule-driven layout
    - Refine getAllActiveTags in Main.lua to prevent generic state tags (e.g., state.Checked) from leaking into the global SetBox environment
    - Update Label.lua to resolve 'text' with a 'title' fallback, ensuring container headers display correctly
    - Add titles to sidebar and debug panel rules in default.lua
    - Improve spring-based layout distribution in Container.lua by ensuring rounded sizes and clamped overrides
    - Resolve VFO and ISG wheel tuning steps by updating MHz to Hz in events.lua
    - Restore missing top-level variables and initialization order in Main.lua
2026-03-08 Fix mirrored images and VFO tuning sync. Correct complex quadrature mixing in twin SignalGen, implement independent power-normalized LMS I/Q correction in DspEngine, and fix VFO property propagation 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
2026-03-08 Optimize calibration accuracy and eliminate 4kHz Nyquist artifact.
    - Implemented Least Squares vector solver for high-precision, one-time calibration.
    - Added persistent alignment weight support to Calibration.lua and DspEngine.
    - Fixed 4kHz pole during stimulus pauses by correctly handling Nyquist energy in upsampleBuffer.
    - Paused regular RF stimulus during calibration to ensure a pure reference tone.
    - Added fmod to DspEngine phase calculation for long-term numerical stability.
2026-03-09 Refactor application architecture to strict MVC with reactive rule projection.
    - Implemented Model.lua with a hierarchical, reactive state structure using polymorphic Type Objects (Number, Bool, String).
    - Created AppController.lua to centralize business logic, VFO-to-Preselector coordination, and batched hardware synchronization.
    - Renamed Dispatch.lua to Hardware.lua, providing a unified HAL with atomic "per-frame" sync to prevent transient hardware states.
    - Integrated SetBox.lua with the Reactive system, enabling automatic dependency tracking and live projection of rules into the Model.
    - Refactored all modular UI widgets to use Dependency Injection, receiving observable references inste
2026-03-10 Implement non-blocking UI architecture and fix preselector state feedback.
    - UI: Moved network command processing and hardware state polling to a background thread to eliminate freezes.
    - UI: Fixed preselector feedback loop; L and C checkboxes now correctly reflect hardware-calculated auto-tune values.
    - UI: Simplified interface by removing non-functional LMS, Matrix Bypass, and Demod Filter checkboxes.
    - App: Decoupled time-critical UDP data processing from synchronous TCP control requests to fix audio clicking.
    - Twin: Standardized state response protocol and implemented immediate auto-tune calculation on SPSA toggle.
    - Twin: Reduced log noise by suppressing periodic GSTA command output.
2026-03-10 app: Fix LSB sideband inversion and DSP pipeline ordering
2026-03-11 app: minor comment style fix in Events.lua
2026-03-11 twin: optimize digital twin performance and fix stimulus aliasing
    - Implement batch stimulus generation and fast Xorwow PRNG to eliminate audio stuttering.
    - Add frequency-dependent preselector gain and bandwidth filtering to prevent aliasing.
    - Implement realistic QSD mixer model with 2nd and 3rd harmonic responses.
    - Optimize RFCapturePlayer with a stateful phasor for upconversion.
2026-03-12 ui: implement horizontal spectrum/waterfall zooming and SignalBox centering
    - Add support for horizontal zooming via '+' and '-' keys (Model.spectrumZoom).
    - Implement automatic centering of the selected SignalBox when zooming.
    - Update OpenGL WaterfallRenderer to support texture-coordinate zooming.
    - Update GraticuleLegend and SignalBox rendering for dynamic spans.
    - Refactor Model.projection to support robust default values and error handling.
    - Update documentation to reflect new zooming and SignalBox behaviors.
2026-03-14 Dumping widget tree now, a little sanity refactoring
2026-03-19 Fix UI layout and event handling, add Slider and Button interaction, and improve Color handling
2026-03-19 Ensure maxPeak is an integer for math.random in Spectrum:draw
2026-03-19 Unify SMeter module and clean up UI naming conventions
    - Merge SMeter calculation logic and UI widget into a single ui/SMeter.lua
    - Update AppController.lua to point to the new unified SMeter module
    - Adopt PascalCase for widget factories and camelCase for instances in Main.lua
    - Remove 'Orig' and 'Original' suffixes from widget variables in Main.lua
    - Promote original radio-specific Slider to primary ui/Slider.lua
    - Remove redundant SMeterCalc.lua and SliderOld.lua
2026-03-20 Fix missing ui.State requirements in several widgets
2026-03-20 Cleanup debug logging and finalize reactive model fixes
    - Remove throttled spectrum data logs from C++ and Lua.
    - Remove hardware synchronization logs from AppController.
    - Fix default RF gain to ensure audible startup (30 dB).
    - Finalize granular property versioning in Model.lua to prevent recursion loops.
    - Ensure spectrum display correctly pulls from global hardware data cache.
2026-03-21 Fix AM distortion, implement command coalescing, and improve UI interaction
2026-03-22 Fix AM distortion by preserving carrier in DC offset correction and aligning Triple-QSD fundamentals
2026-03-25 Checkpoint before crazy script screws my files up (again)
2026-03-26 Add RGB LED on STM32 GPIOs. Clean up via moats.
2026-04-18 Checkpoint before maybe transitioning to fully differential QSDs and different bandpass filtering strategy
2026-04-30 Move to new BPFs+HPF, add DC blocking caps for AS183-92LF switches in groups, fix miswiring of QSDs (!)
